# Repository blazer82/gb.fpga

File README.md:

[![verilator-lint-badge]](https://github.com/blazer82/gb.fpga/actions?workflow=verilator-lint)

# FPGAMB0 - FPGA-based Handheld Console

This repository contains the PCB design files as well as the HDL sources for an FPGA-based handheld console that plays games from Gameboy cartridges.

## Demo (GIF)

## Testbenches

Testbench files can be run and analyzed using _iverilog_ and _GTKWave_:

```
iverilog -o main src/hdl/ascii_encoder_tb.v && vvp main -lxt2 && open dump.lx2
```

[verilator-lint-badge]: https://github.com/blazer82/gb.fpga/workflows/verilator-lint/badge.svg

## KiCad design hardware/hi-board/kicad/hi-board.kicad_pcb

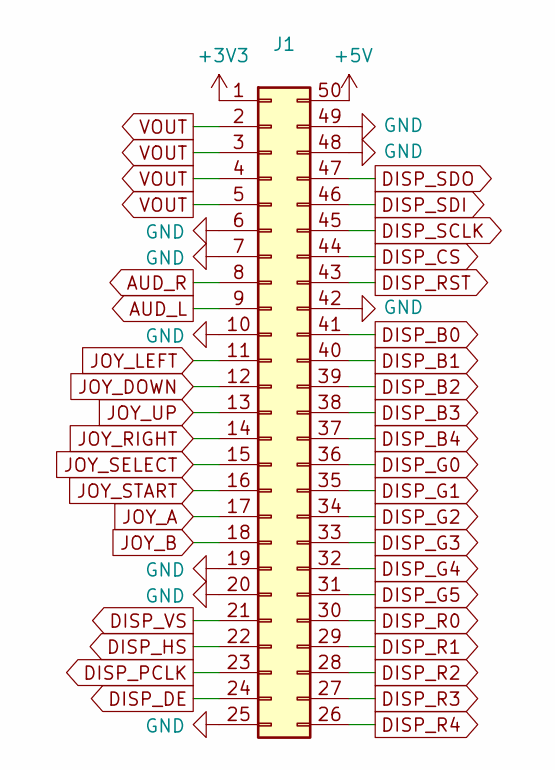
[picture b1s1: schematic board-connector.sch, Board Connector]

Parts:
J1: Conn_02x25_Counter_Clockwise; Hirose_FH12-50S-0.5SH_1x50-1MP_P0.50mm_Horizontal

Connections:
unnamed: J1.2, J1.3, J1.4, J1.5
unnamed: J1.6, J1.7, J1.10, J1.19, J1.20, J1.25, J1.42, J1.48, J1.49

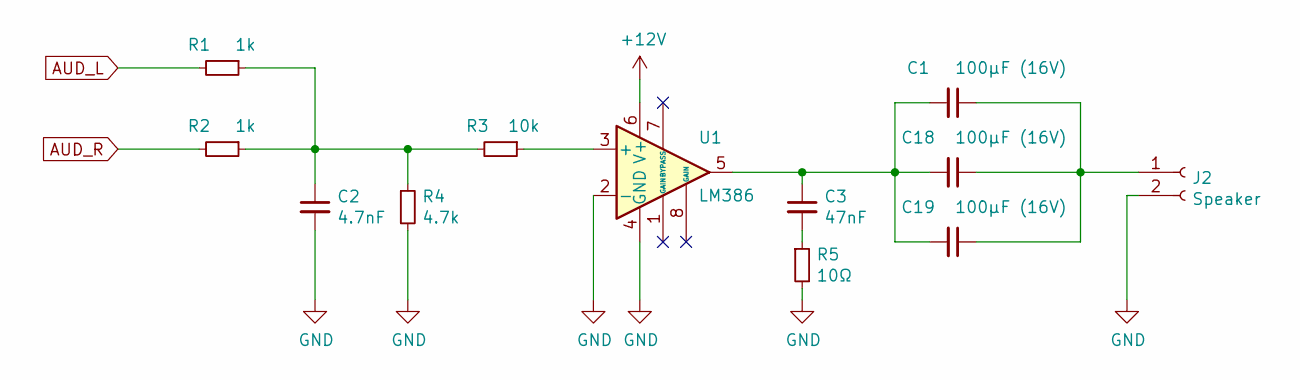
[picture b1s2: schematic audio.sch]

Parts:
C1, C18, C19: 100µF (16V); C_1210_3225Metric
C2: 4.7nF; C_0603_1608Metric
C3: 47nF; C_0603_1608Metric
J2: Speaker; PinHeader_1x02_P2.54mm_Vertical
R1, R2: 1k; R_0603_1608Metric
R3: 10k; R_0603_1608Metric
R4: 4.7k; R_0603_1608Metric
R5: 10Ω; R_0603_1608Metric
U1: LM386; VSSOP-8_3.0x3.0mm_P0.65mm

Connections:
+12V: U1.6 (V+); also elsewhere on the board
AUD_L: R1.2; also elsewhere on the board
AUD_R: R2.2; also elsewhere on the board
GND: C2.2, J2.2, R4.2, R5.2, U1.2 (-), U1.4 (GND); also elsewhere on the board
unnamed: C1.1, C18.1, C19.1, J2.1
unnamed: C1.2, C3.1, C18.2, C19.2, U1.5
unnamed: C2.1, R1.1, R2.1, R3.2, R4.1
unnamed: C3.2, R5.1
unnamed: R3.1, U1.3 (+)

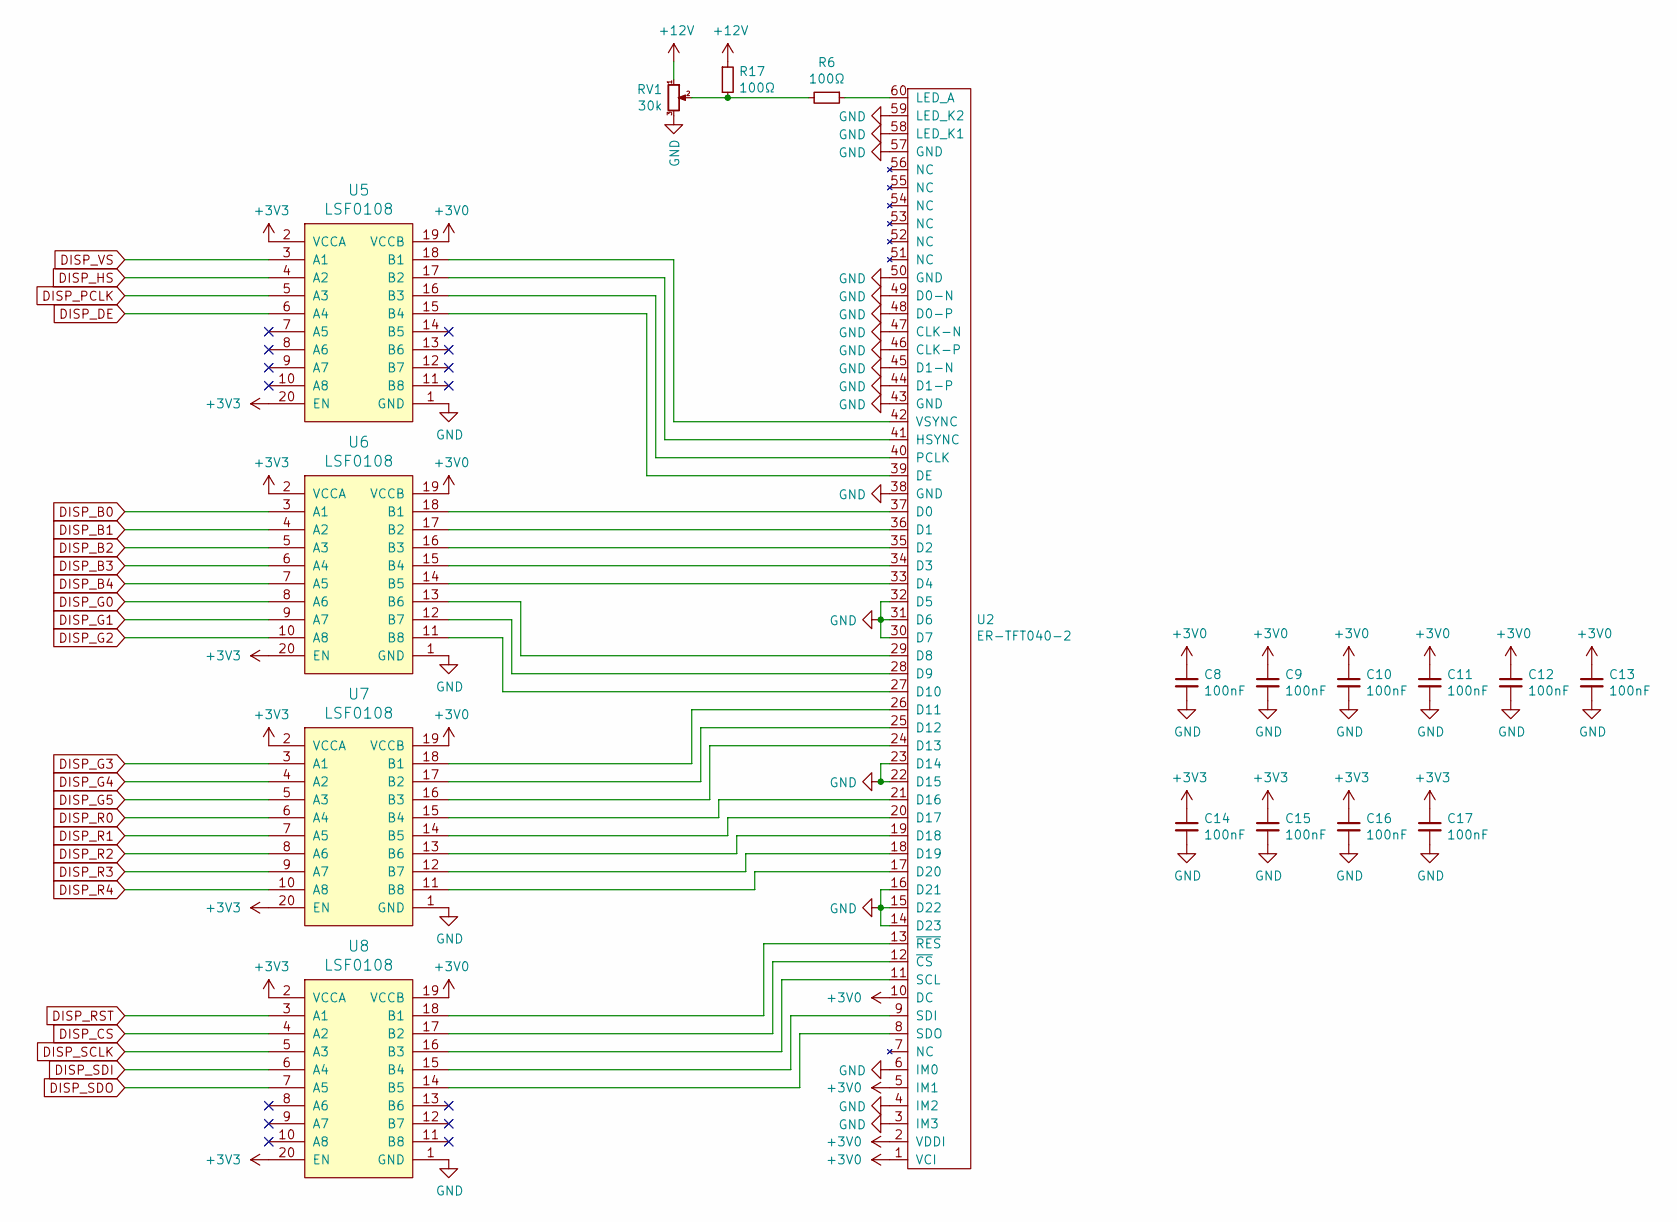
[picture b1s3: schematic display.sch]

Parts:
C8, C9, C10, C11, C12, C13, C14, C15, C16, C17: 100nF; C_0603_1608Metric
R6, R17: 100Ω; R_0603_1608Metric
RV1: 30k; Dual_Pot
U2: ER-TFT040-2; HRS_FH28-60S-0.5SH(05)
U5, U6, U7, U8: LSF0108; TSSOP-20_4.4x6.5mm_P0.65mm

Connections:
+3V0: C8.1, C9.1, C10.1, C11.1, C12.1, C13.1, U2.1 (VCI), U2.2 (VDDI), U2.5 (IM1), U2.10 (DC), U5.19 (VCCB), U6.19 (VCCB), U7.19 (VCCB), U8.19 (VCCB); also elsewhere on the board
+3V3: C14.1, C15.1, C16.1, C17.1, U5.2 (VCCA), U5.20 (EN), U6.2 (VCCA), U6.20 (EN), U7.2 (VCCA), U7.20 (EN), U8.2 (VCCA), U8.20 (EN); also elsewhere on the board
+12V: R17.1, RV1.1; also elsewhere on the board
DISP_B0: U6.3 (A1); also elsewhere on the board
DISP_B1: U6.4 (A2); also elsewhere on the board
DISP_B2: U6.5 (A3); also elsewhere on the board
DISP_B3: U6.6 (A4); also elsewhere on the board
DISP_B4: U6.7 (A5); also elsewhere on the board
DISP_CS: U8.4 (A2); also elsewhere on the board
DISP_DE: U5.6 (A4); also elsewhere on the board
DISP_G0: U6.8 (A6); also elsewhere on the board
DISP_G1: U6.9 (A7); also elsewhere on the board
DISP_G2: U6.10 (A8); also elsewhere on the board
DISP_G3: U7.3 (A1); also elsewhere on the board
DISP_G4: U7.4 (A2); also elsewhere on the board
DISP_G5: U7.5 (A3); also elsewhere on the board
DISP_HS: U5.4 (A2); also elsewhere on the board
DISP_PCLK: U5.5 (A3); also elsewhere on the board
DISP_R0: U7.6 (A4); also elsewhere on the board
DISP_R1: U7.7 (A5); also elsewhere on the board
DISP_R2: U7.8 (A6); also elsewhere on the board
DISP_R3: U7.9 (A7); also elsewhere on the board
DISP_R4: U7.10 (A8); also elsewhere on the board
DISP_RST: U8.3 (A1); also elsewhere on the board
DISP_SCLK: U8.5 (A3); also elsewhere on the board
DISP_SDI: U8.6 (A4); also elsewhere on the board
DISP_SDO: U8.7 (A5); also elsewhere on the board
DISP_VS: U5.3 (A1); also elsewhere on the board
GND: C8.2, C9.2, C10.2, C11.2, C12.2, C13.2, C14.2, C15.2, C16.2, C17.2, RV1.3, U2.3 (IM3), U2.4 (IM2), U2.6 (IM0), U2.14 (D23), U2.15 (D22), U2.16 (D21), U2.22 (D15), U2.23 (D14), U2.30 (D7), U2.31 (D6), U2.32 (D5), U2.38 (GND), U2.43 (GND), U2.44 (D1-P), U2.45 (D1-N), U2.46 (CLK-P), U2.47 (CLK-N), U2.48 (D0-P), U2.49 (D0-N), U2.50 (GND), U2.57 (GND), U2.58 (LED_K1), U2.59 (LED_K2), U5.1 (GND), U6.1 (GND), U7.1 (GND), U8.1 (GND); also elsewhere on the board
unnamed 48: R6.1, U2.60 (LED_A); also elsewhere on the board
unnamed: R6.2, R17.2, RV1.2
unnamed 55: U2.8 (SDO), U8.14 (B5); also elsewhere on the board
unnamed 56: U2.9 (SDI), U8.15 (B4); also elsewhere on the board
unnamed 57: U2.11 (SCL), U8.16 (B3); also elsewhere on the board
unnamed 58: U2.12 (~CS), U8.17 (B2); also elsewhere on the board
unnamed 59: U2.13 (~RES), U8.18 (B1); also elsewhere on the board
unnamed 60: U2.17 (D20), U7.11 (B8); also elsewhere on the board
unnamed 61: U2.18 (D19), U7.12 (B7); also elsewhere on the board
unnamed 62: U2.19 (D18), U7.13 (B6); also elsewhere on the board
unnamed 63: U2.20 (D17), U7.14 (B5); also elsewhere on the board
unnamed 64: U2.21 (D16), U7.15 (B4); also elsewhere on the board
unnamed 65: U2.24 (D13), U7.16 (B3); also elsewhere on the board
unnamed 66: U2.25 (D12), U7.17 (B2); also elsewhere on the board
unnamed 67: U2.26 (D11), U7.18 (B1); also elsewhere on the board
unnamed 68: U2.27 (D10), U6.11 (B8); also elsewhere on the board
unnamed 69: U2.28 (D9), U6.12 (B7); also elsewhere on the board
unnamed 70: U2.29 (D8), U6.13 (B6); also elsewhere on the board
unnamed 71: U2.33 (D4), U6.14 (B5); also elsewhere on the board
unnamed 72: U2.34 (D3), U6.15 (B4); also elsewhere on the board
unnamed 73: U2.35 (D2), U6.16 (B3); also elsewhere on the board
unnamed 74: U2.36 (D1), U6.17 (B2); also elsewhere on the board
unnamed 75: U2.37 (D0), U6.18 (B1); also elsewhere on the board
unnamed 76: U2.39 (DE), U5.15 (B4); also elsewhere on the board
unnamed 77: U2.40 (PCLK), U5.16 (B3); also elsewhere on the board
unnamed 78: U2.41 (HSYNC), U5.17 (B2); also elsewhere on the board
unnamed 79: U2.42 (VSYNC), U5.18 (B1); also elsewhere on the board

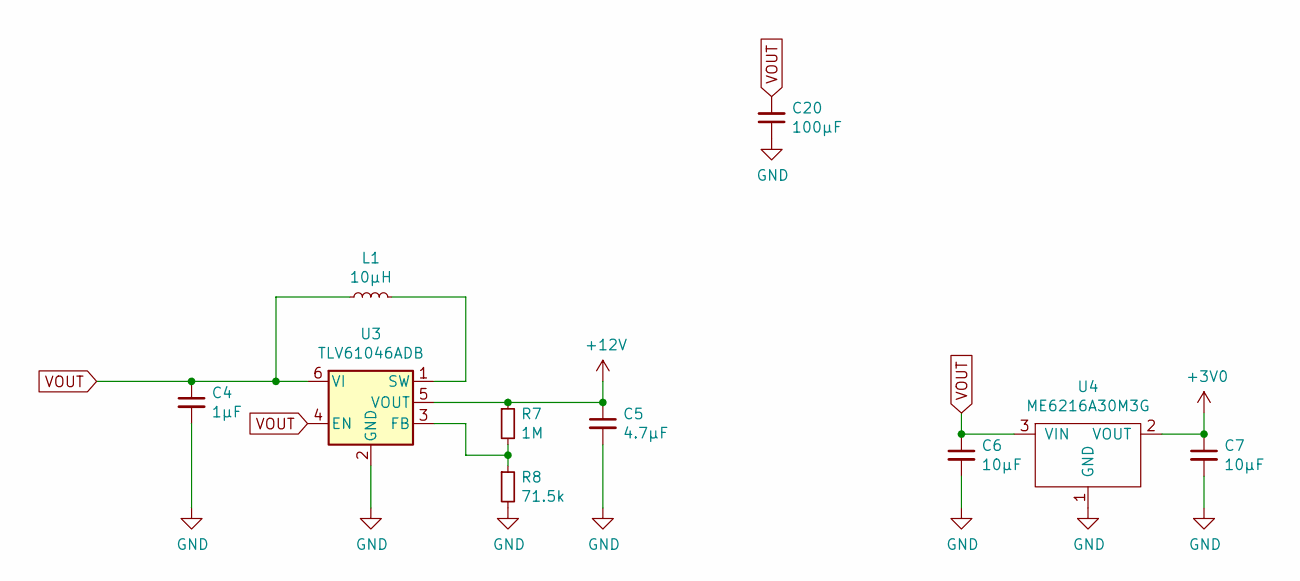
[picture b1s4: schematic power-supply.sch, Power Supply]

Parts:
C4: 1µF; C_0603_1608Metric
C5: 4.7µF; C_0603_1608Metric
C6, C7: 10µF; C_0603_1608Metric
C20: 100µF; C_1210_3225Metric
L1: 10µH; L_0603_1608Metric
R7: 1M; R_0603_1608Metric
R8: 71.5k; R_0603_1608Metric
U3: TLV61046ADB; SOT-23-6
U4: ME6216A30M3G; SOT-23

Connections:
+3V0: C7.1, U4.2 (VOUT); also elsewhere on the board
+12V: C5.1, R7.1, U3.5 (VOUT); also elsewhere on the board
GND: C4.2, C5.2, C6.2, C7.2, C20.1, R8.2, U3.2 (GND), U4.1 (GND); also elsewhere on the board
unnamed: L1.2, U3.1 (SW)
unnamed: R7.2, R8.1, U3.3 (FB)
VOUT: C4.1, C6.1, C20.2, L1.1, U3.4 (EN), U3.6 (VI), U4.3 (VIN); also elsewhere on the board

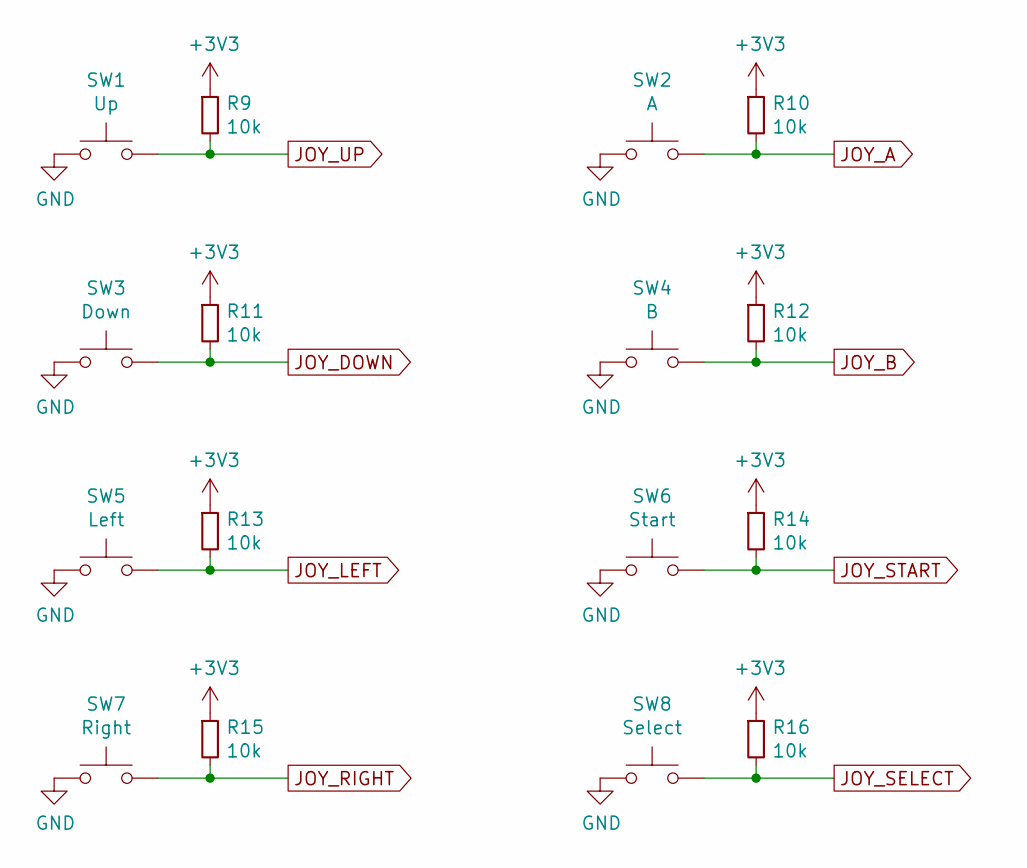
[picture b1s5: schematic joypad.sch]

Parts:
R9, R10, R11, R12, R13, R14, R15, R16: 10k; R_0603_1608Metric
SW1: Up; Rubber_Round
SW2: A; Rubber_Round
SW3: Down; Rubber_Round
SW4: B; Rubber_Round
SW5: Left; Rubber_Round
SW6: Start; Rubber_Square
SW7: Right; Rubber_Round
SW8: Select; Rubber_Square

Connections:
+3V3: R9.1, R10.1, R11.1, R12.1, R13.1, R14.1, R15.1, R16.1; also elsewhere on the board
GND: SW1.1, SW2.1, SW3.1, SW4.1, SW5.1, SW6.1, SW7.1, SW8.1; also elsewhere on the board
JOY_A: R10.2, SW2.2; also elsewhere on the board
JOY_B: R12.2, SW4.2; also elsewhere on the board
JOY_DOWN: R11.2, SW3.2; also elsewhere on the board
JOY_LEFT: R13.2, SW5.2; also elsewhere on the board
JOY_RIGHT: R15.2, SW7.2; also elsewhere on the board
JOY_SELECT: R16.2, SW8.2; also elsewhere on the board
JOY_START: R14.2, SW6.2; also elsewhere on the board
JOY_UP: R9.2, SW1.2; also elsewhere on the board

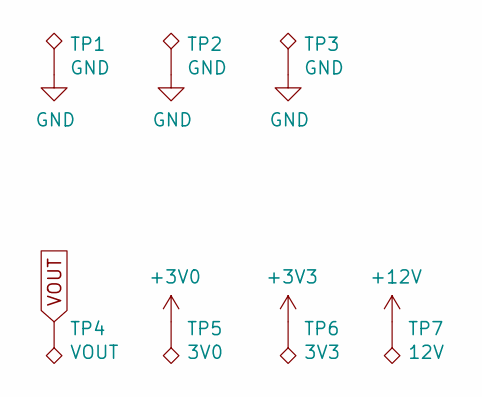
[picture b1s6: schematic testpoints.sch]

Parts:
TP1, TP2, TP3: GND; TestPoint_THTPad_1.5x1.5mm_Drill0.7mm
TP4: VOUT; TestPoint_THTPad_1.0x1.0mm_Drill0.5mm
TP5: 3V0; TestPoint_THTPad_1.0x1.0mm_Drill0.5mm
TP6: 3V3; TestPoint_THTPad_1.0x1.0mm_Drill0.5mm
TP7: 12V; TestPoint_THTPad_1.0x1.0mm_Drill0.5mm

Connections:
+3V0: TP5.1; also elsewhere on the board
+3V3: TP6.1; also elsewhere on the board
+12V: TP7.1; also elsewhere on the board
GND: TP1.1, TP2.1, TP3.1; also elsewhere on the board
VOUT: TP4.1; also elsewhere on the board

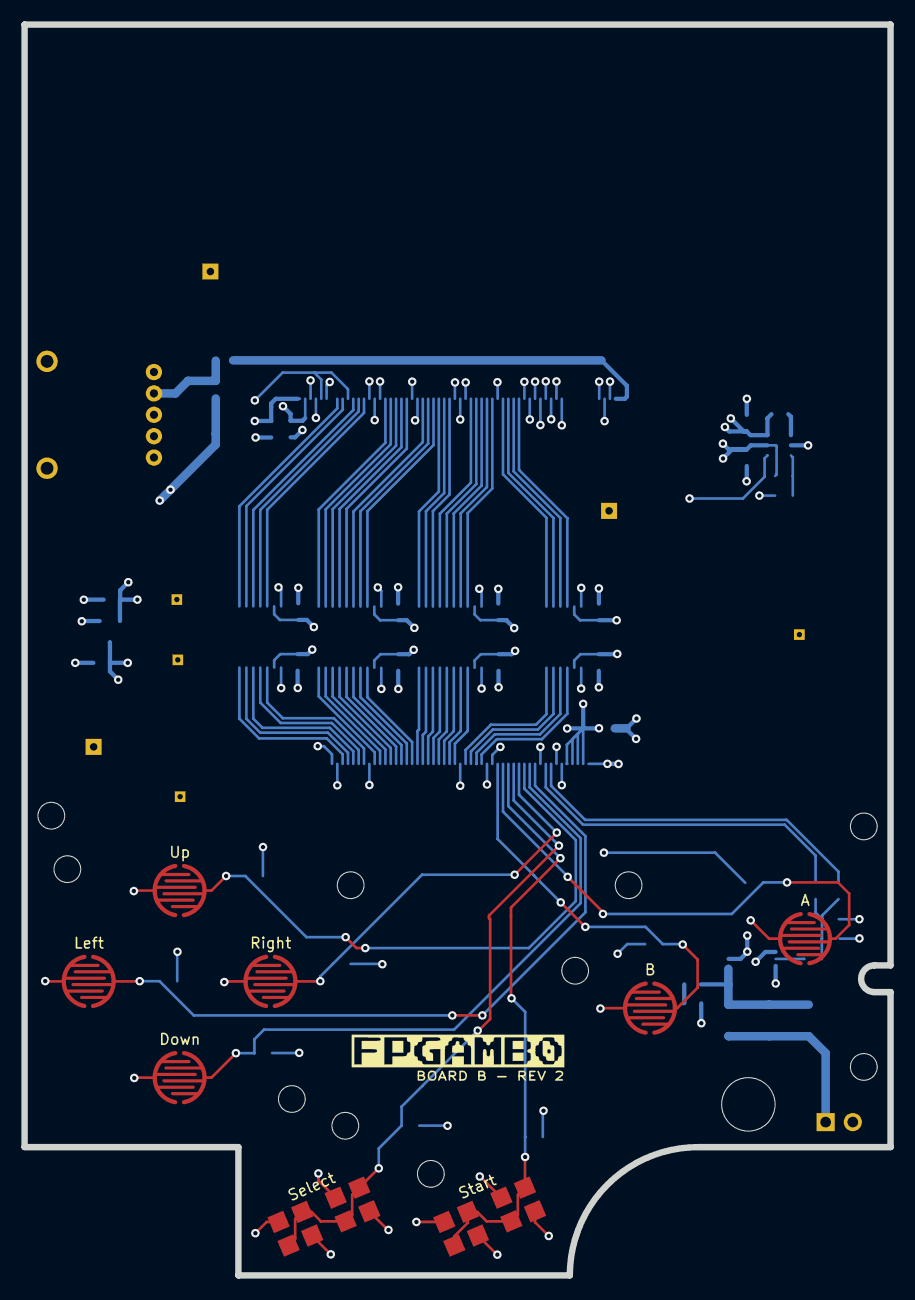
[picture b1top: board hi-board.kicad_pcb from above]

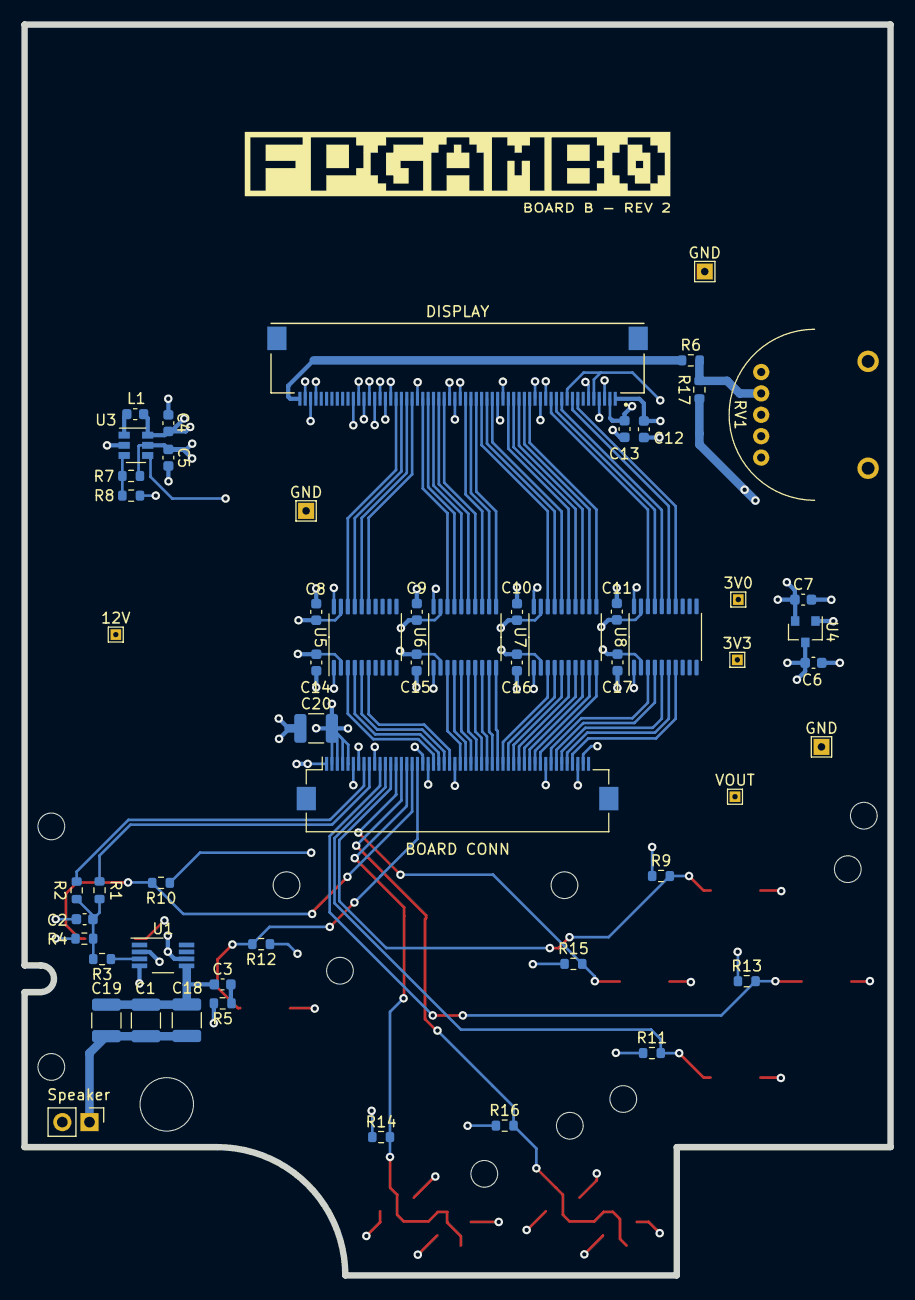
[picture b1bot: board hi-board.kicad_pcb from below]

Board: 4 copper layers, 81.0 x 117.0 mm, 64 parts (56 on the bottom side), 74 nets.

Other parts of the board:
BOARD CONN: Conn_02x25_Counter_Clockwise; Hirose_FH12-50S-0.5SH_1x50-1MP_P0.50mm_Horizontal
DISPLAY: ER-TFT040-2; HRS_FH28-60S-0.5SH(05)

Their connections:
+3V0: DISPLAY.1, DISPLAY.2, DISPLAY.5, DISPLAY.10; also elsewhere on the board
+3V3: BOARD CONN.1; also elsewhere on the board
AUD_L: BOARD CONN.9; also elsewhere on the board
AUD_R: BOARD CONN.8; also elsewhere on the board
DISP_B0: BOARD CONN.26; also elsewhere on the board
DISP_B1: BOARD CONN.27; also elsewhere on the board
DISP_B2: BOARD CONN.28; also elsewhere on the board
DISP_B3: BOARD CONN.29; also elsewhere on the board
DISP_B4: BOARD CONN.30; also elsewhere on the board
DISP_CS: BOARD CONN.44; also elsewhere on the board
DISP_DE: BOARD CONN.24; also elsewhere on the board
DISP_G0: BOARD CONN.31; also elsewhere on the board
DISP_G1: BOARD CONN.32; also elsewhere on the board
DISP_G2: BOARD CONN.33; also elsewhere on the board
DISP_G3: BOARD CONN.34; also elsewhere on the board
DISP_G4: BOARD CONN.35; also elsewhere on the board
DISP_G5: BOARD CONN.36; also elsewhere on the board
DISP_HS: BOARD CONN.22; also elsewhere on the board
DISP_PCLK: BOARD CONN.23; also elsewhere on the board
DISP_R0: BOARD CONN.37; also elsewhere on the board
DISP_R1: BOARD CONN.38; also elsewhere on the board
DISP_R2: BOARD CONN.39; also elsewhere on the board
DISP_R3: BOARD CONN.40; also elsewhere on the board
DISP_R4: BOARD CONN.41; also elsewhere on the board
DISP_RST: BOARD CONN.43; also elsewhere on the board
DISP_SCLK: BOARD CONN.45; also elsewhere on the board
DISP_SDI: BOARD CONN.46; also elsewhere on the board
DISP_SDO: BOARD CONN.47; also elsewhere on the board
DISP_VS: BOARD CONN.21; also elsewhere on the board
GND: BOARD CONN.6, BOARD CONN.7, BOARD CONN.10, BOARD CONN.19, BOARD CONN.20, BOARD CONN.25, BOARD CONN.42, BOARD CONN.48, BOARD CONN.49, DISPLAY.3, DISPLAY.4, DISPLAY.6, DISPLAY.14, DISPLAY.15, DISPLAY.16, DISPLAY.22, DISPLAY.23, DISPLAY.30, DISPLAY.31, DISPLAY.32, DISPLAY.38, DISPLAY.43, DISPLAY.44, DISPLAY.45, DISPLAY.46, DISPLAY.47, DISPLAY.48, DISPLAY.49, DISPLAY.50, DISPLAY.57, DISPLAY.58, DISPLAY.59; also elsewhere on the board
JOY_A: BOARD CONN.17; also elsewhere on the board
JOY_B: BOARD CONN.18; also elsewhere on the board
JOY_DOWN: BOARD CONN.12; also elsewhere on the board
JOY_LEFT: BOARD CONN.11; also elsewhere on the board
JOY_RIGHT: BOARD CONN.14; also elsewhere on the board
JOY_SELECT: BOARD CONN.15; also elsewhere on the board
JOY_START: BOARD CONN.16; also elsewhere on the board
JOY_UP: BOARD CONN.13; also elsewhere on the board
unnamed 48: DISPLAY.60; also elsewhere on the board
unnamed 55: DISPLAY.8; also elsewhere on the board
unnamed 56: DISPLAY.9; also elsewhere on the board
unnamed 57: DISPLAY.11; also elsewhere on the board
unnamed 58: DISPLAY.12; also elsewhere on the board
unnamed 59: DISPLAY.13; also elsewhere on the board
unnamed 60: DISPLAY.17; also elsewhere on the board
unnamed 61: DISPLAY.18; also elsewhere on the board
unnamed 62: DISPLAY.19; also elsewhere on the board
unnamed 63: DISPLAY.20; also elsewhere on the board
unnamed 64: DISPLAY.21; also elsewhere on the board
unnamed 65: DISPLAY.24; also elsewhere on the board
unnamed 66: DISPLAY.25; also elsewhere on the board
unnamed 67: DISPLAY.26; also elsewhere on the board
unnamed 68: DISPLAY.27; also elsewhere on the board
unnamed 69: DISPLAY.28; also elsewhere on the board
unnamed 70: DISPLAY.29; also elsewhere on the board
unnamed 71: DISPLAY.33; also elsewhere on the board
unnamed 72: DISPLAY.34; also elsewhere on the board
unnamed 73: DISPLAY.35; also elsewhere on the board
unnamed 74: DISPLAY.36; also elsewhere on the board
unnamed 75: DISPLAY.37; also elsewhere on the board
unnamed 76: DISPLAY.39; also elsewhere on the board
unnamed 77: DISPLAY.40; also elsewhere on the board
unnamed 78: DISPLAY.41; also elsewhere on the board
unnamed 79: DISPLAY.42; also elsewhere on the board
VOUT: BOARD CONN.2, BOARD CONN.3, BOARD CONN.4, BOARD CONN.5; also elsewhere on the board

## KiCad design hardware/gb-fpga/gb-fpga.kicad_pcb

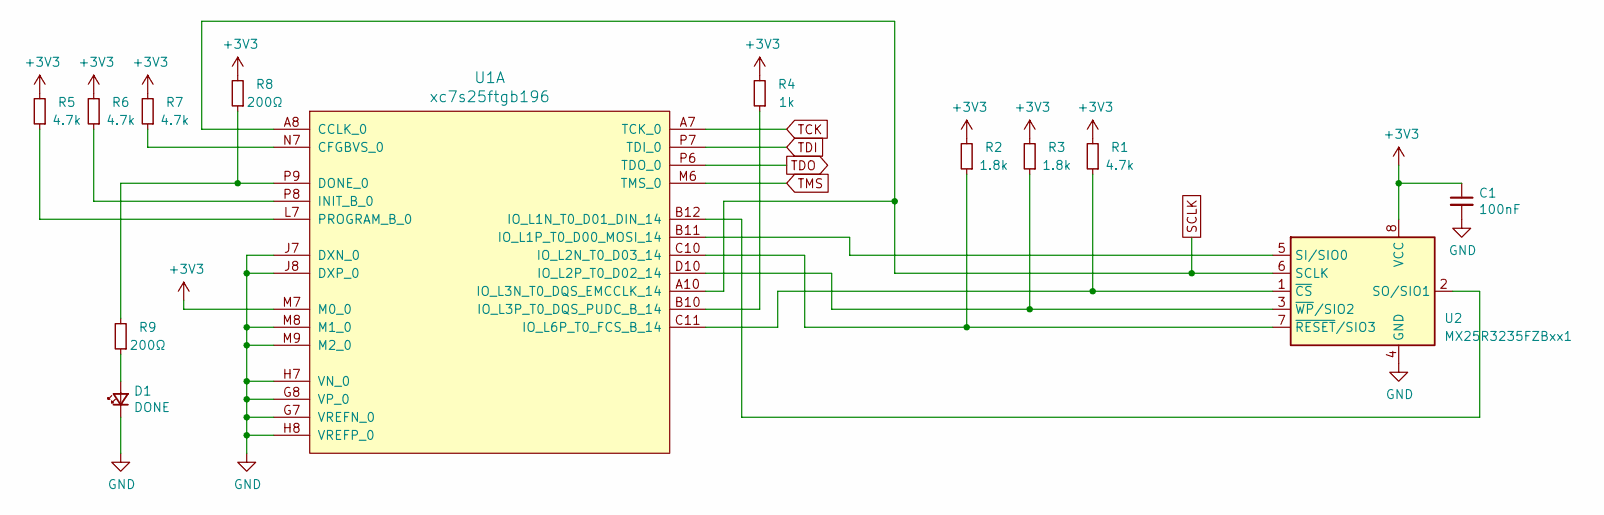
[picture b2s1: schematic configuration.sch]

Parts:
C1: 100nF; C_0402_1005Metric; Manufacturer Part Number CL05B104KO5NNNC
D1: DONE; LED_0402_1005Metric; Manufacturer Part Number NCD0402G1
R1, R5, R6, R7: 4.7k; R_0402_1005Metric; Manufacturer Part Number RC0402JR-074K7L
R2, R3: 1.8k; R_0402_1005Metric; Manufacturer Part Number RC0402JR-071K8L
R4: 1k; R_0402_1005Metric; Manufacturer Part Number RC0402JR-071KL
R8, R9: 200Ω; R_0402_1005Metric; Manufacturer Part Number AC0402JR-07200RL
U1: xc7s25ftgb196; Manufacturer Part Number XC7S25-1FTGB196C
U2: MX25R3235FZBxx1; USON-8_4.0x3.0mm_P0.8mm; Manufacturer Part Number MX25R3235FZBIL0

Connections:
+3V3: C1.1, R1.2, R2.2, R3.2, R4.2, R5.2, R6.2, R7.2, R8.2, U1.M7 (M0_0), U2.8 (VCC); also elsewhere on the board
GND: C1.2, D1.1 (K), U1.G7 (VREFN_0), U1.G8 (VP_0), U1.H7 (VN_0), U1.H8 (VREFP_0), U1.J7 (DXN_0), U1.J8 (DXP_0), U1.M8 (M1_0), U1.M9 (M2_0), U2.4 (GND), U2.9 (GND); also elsewhere on the board
unnamed: D1.2 (A), R9.1
unnamed: R1.1, U1.C11 (IO_L6P_T0_FCS_B_14), U2.1 (~CS)
unnamed: R2.1, U1.C10 (IO_L2N_T0_D03_14), U2.7 (~RESET~/SIO3)
unnamed: R3.1, U1.D10 (IO_L2P_T0_D02_14), U2.3 (~WP~/SIO2)
unnamed: R4.1, U1.B10 (IO_L3P_T0_DQS_PUDC_B_14)
unnamed: R5.1, U1.L7 (PROGRAM_B_0)
unnamed: R6.1, U1.P8 (INIT_B_0)
unnamed: R7.1, U1.N7 (CFGBVS_0)
unnamed: R8.1, R9.2, U1.P9 (DONE_0)
unnamed: U1.B11 (IO_L1P_T0_D00_MOSI_14), U2.5 (SI/SIO0)
unnamed: U1.B12 (IO_L1N_T0_D01_DIN_14), U2.2 (SO/SIO1)
SCLK: U1.A8 (CCLK_0), U1.A10 (IO_L3N_T0_DQS_EMCCLK_14), U2.6 (SCLK); also elsewhere on the board
TCK: U1.A7 (TCK_0); also elsewhere on the board
TDI: U1.P7 (TDI_0); also elsewhere on the board
TDO: U1.P6 (TDO_0); also elsewhere on the board
TMS: U1.M6 (TMS_0); also elsewhere on the board

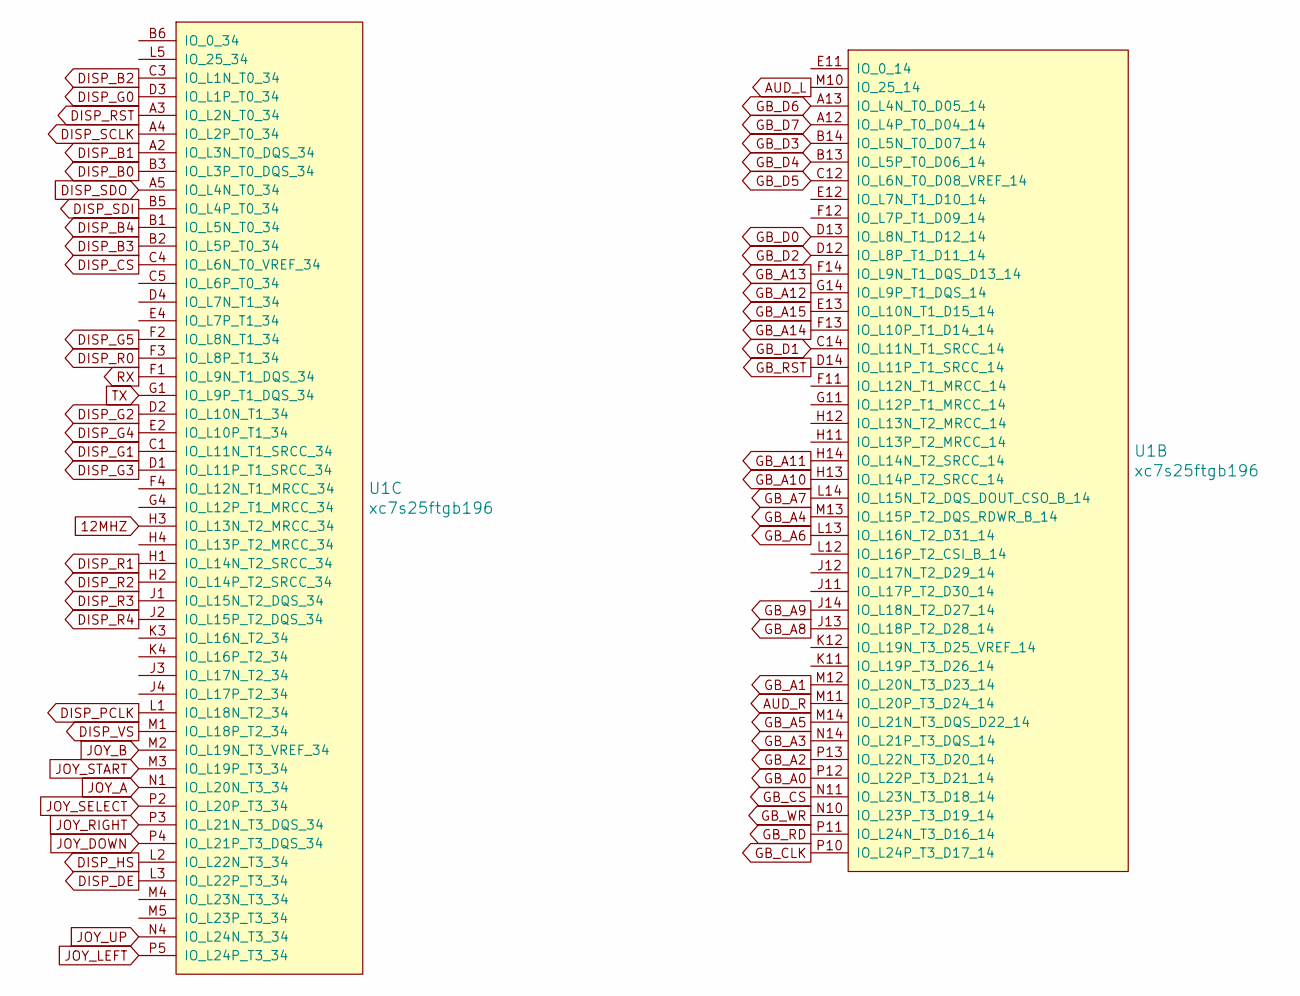
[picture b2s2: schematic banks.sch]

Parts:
U1: xc7s25ftgb196

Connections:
12MHZ: U1.H3 (IO_L13N_T2_MRCC_34); also elsewhere on the board
AUD_L: U1.M10 (IO_25_14); also elsewhere on the board
AUD_R: U1.M11 (IO_L20P_T3_D24_14); also elsewhere on the board
DISP_B0: U1.B3 (IO_L3P_T0_DQS_34); also elsewhere on the board
DISP_B1: U1.A2 (IO_L3N_T0_DQS_34); also elsewhere on the board
DISP_B2: U1.C3 (IO_L1N_T0_34); also elsewhere on the board
DISP_B3: U1.B2 (IO_L5P_T0_34); also elsewhere on the board
DISP_B4: U1.B1 (IO_L5N_T0_34); also elsewhere on the board
DISP_CS: U1.C4 (IO_L6N_T0_VREF_34); also elsewhere on the board
DISP_DE: U1.L3 (IO_L22P_T3_34); also elsewhere on the board
DISP_G0: U1.D3 (IO_L1P_T0_34); also elsewhere on the board
DISP_G1: U1.C1 (IO_L11N_T1_SRCC_34); also elsewhere on the board
DISP_G2: U1.D2 (IO_L10N_T1_34); also elsewhere on the board
DISP_G3: U1.D1 (IO_L11P_T1_SRCC_34); also elsewhere on the board
DISP_G4: U1.E2 (IO_L10P_T1_34); also elsewhere on the board
DISP_G5: U1.F2 (IO_L8N_T1_34); also elsewhere on the board
DISP_HS: U1.L2 (IO_L22N_T3_34); also elsewhere on the board
DISP_PCLK: U1.L1 (IO_L18N_T2_34); also elsewhere on the board
DISP_R0: U1.F3 (IO_L8P_T1_34); also elsewhere on the board
DISP_R1: U1.H1 (IO_L14N_T2_SRCC_34); also elsewhere on the board
DISP_R2: U1.H2 (IO_L14P_T2_SRCC_34); also elsewhere on the board
DISP_R3: U1.J1 (IO_L15N_T2_DQS_34); also elsewhere on the board
DISP_R4: U1.J2 (IO_L15P_T2_DQS_34); also elsewhere on the board
DISP_RST: U1.A3 (IO_L2N_T0_34); also elsewhere on the board
DISP_SCLK: U1.A4 (IO_L2P_T0_34); also elsewhere on the board
DISP_SDI: U1.B5 (IO_L4P_T0_34); also elsewhere on the board
DISP_SDO: U1.A5 (IO_L4N_T0_34); also elsewhere on the board
DISP_VS: U1.M1 (IO_L18P_T2_34); also elsewhere on the board
GB_A0: U1.P12 (IO_L22P_T3_D21_14); also elsewhere on the board
GB_A1: U1.M12 (IO_L20N_T3_D23_14); also elsewhere on the board
GB_A2: U1.P13 (IO_L22N_T3_D20_14); also elsewhere on the board
GB_A3: U1.N14 (IO_L21P_T3_DQS_14); also elsewhere on the board
GB_A4: U1.M13 (IO_L15P_T2_DQS_RDWR_B_14); also elsewhere on the board
GB_A5: U1.M14 (IO_L21N_T3_DQS_D22_14); also elsewhere on the board
GB_A6: U1.L13 (IO_L16N_T2_D31_14); also elsewhere on the board
GB_A7: U1.L14 (IO_L15N_T2_DQS_DOUT_CSO_B_14); also elsewhere on the board
GB_A8: U1.J13 (IO_L18P_T2_D28_14); also elsewhere on the board
GB_A9: U1.J14 (IO_L18N_T2_D27_14); also elsewhere on the board
GB_A10: U1.H13 (IO_L14P_T2_SRCC_14); also elsewhere on the board
GB_A11: U1.H14 (IO_L14N_T2_SRCC_14); also elsewhere on the board
GB_A12: U1.G14 (IO_L9P_T1_DQS_14); also elsewhere on the board
GB_A13: U1.F14 (IO_L9N_T1_DQS_D13_14); also elsewhere on the board
GB_A14: U1.F13 (IO_L10P_T1_D14_14); also elsewhere on the board
GB_A15: U1.E13 (IO_L10N_T1_D15_14); also elsewhere on the board
GB_CLK: U1.P10 (IO_L24P_T3_D17_14); also elsewhere on the board
GB_CS: U1.N11 (IO_L23N_T3_D18_14); also elsewhere on the board
GB_D0: U1.D13 (IO_L8N_T1_D12_14); also elsewhere on the board
GB_D1: U1.C14 (IO_L11N_T1_SRCC_14); also elsewhere on the board
GB_D2: U1.D12 (IO_L8P_T1_D11_14); also elsewhere on the board
GB_D3: U1.B14 (IO_L5N_T0_D07_14); also elsewhere on the board
GB_D4: U1.B13 (IO_L5P_T0_D06_14); also elsewhere on the board
GB_D5: U1.C12 (IO_L6N_T0_D08_VREF_14); also elsewhere on the board
GB_D6: U1.A13 (IO_L4N_T0_D05_14); also elsewhere on the board
GB_D7: U1.A12 (IO_L4P_T0_D04_14); also elsewhere on the board
GB_RD: U1.P11 (IO_L24N_T3_D16_14); also elsewhere on the board
GB_RST: U1.D14 (IO_L11P_T1_SRCC_14); also elsewhere on the board
GB_WR: U1.N10 (IO_L23P_T3_D19_14); also elsewhere on the board
JOY_A: U1.N1 (IO_L20N_T3_34); also elsewhere on the board
JOY_B: U1.M2 (IO_L19N_T3_VREF_34); also elsewhere on the board
JOY_DOWN: U1.P4 (IO_L21P_T3_DQS_34); also elsewhere on the board
JOY_LEFT: U1.P5 (IO_L24P_T3_34); also elsewhere on the board
JOY_RIGHT: U1.P3 (IO_L21N_T3_DQS_34); also elsewhere on the board
JOY_SELECT: U1.P2 (IO_L20P_T3_34); also elsewhere on the board
JOY_START: U1.M3 (IO_L19P_T3_34); also elsewhere on the board
JOY_UP: U1.N4 (IO_L24N_T3_34); also elsewhere on the board
RX: U1.F1 (IO_L9N_T1_DQS_34); also elsewhere on the board
TX: U1.G1 (IO_L9P_T1_DQS_34); also elsewhere on the board

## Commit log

2021-06-20 Initial
2021-06-20 Add project tcl
2021-06-21 Assign footprint and place fpga on board
2021-06-21 Basic boards setup
2021-06-21 Improve audio output by inversing the pwm counter
2021-06-21 Add physical reset button
2021-06-22 Add hierarchical sheets
2021-06-22 Add GND net
2021-06-22 Use USON footprint for flash memory
2021-06-22 Use human readable names on pcb
2021-06-23 Add board outline
2021-06-23 Move board origin to 0 0
2021-06-23 Add second mounting hole
2021-06-23 Add usb parts
2021-06-23 Add additional mounting holes
2021-06-23 Changes to pcb file
2021-06-23 Add and place cartridge footprint and place usb connector
2021-06-24 Add mounting holes to cartridge footprint
2021-06-24 Rename cartridge symbol
2021-06-24 Add connections to flash ic
2021-06-24 Add local fpga symbol
2021-06-24 Connect flash config circuit
2021-06-25 Replace micro usb with usb type c connector
2021-06-25 Update flash footprint
2021-06-25 Add USB connections
2021-06-26 Add oscillator
2021-06-26 Label cartridge connections
2021-06-26 Add LTC3555
2021-06-27 Add step-down conversion
2021-06-27 Add reverse polarity protection to usb
2021-06-27 Update power circuit
2021-06-27 Use power up sequence recommended for Spartan FPGA
2021-06-28 Switch from 0603 to 0402 footprints
2021-06-28 Add chargeing indicator LED
2021-06-28 Add 5V voltage regulator
2021-06-29 Add capacitor networks to fpga power rails
2021-06-30 Hook up cartridge to translation ics
2021-07-01 Fix cartridge pin out and replace voltage translators
2021-07-01 Add power switch
2021-07-01 Add board connector
2021-07-01 Add signals to board connector
2021-07-02 Add audio filter and volume control to schematic
2021-07-02 Add missing power supplies
2021-07-02 Add volume control footprint
2021-07-03 Update board setup
2021-07-03 Fix volume control pinout
2021-07-03 Fix moved edge cut
2021-07-03 Increase edge cut thickness to increase edge clearance
2021-07-03 Layout some smaller groups
2021-07-03 Place more components
2021-07-04 Place power components
2021-07-04 Fan out part of BGA
2021-07-04 Fan out cartridge pins
2021-07-04 Switch to 0201 footprints for fpga power caps
2021-07-04 Place most fpga caps
2021-07-04 Assign cartridge pins to fpga
2021-07-04 Fan out board connector pins
2021-07-04 Assign board connector pins to fpga
2021-07-04 Fan out the remaining pins
2021-07-05 Layout more components
2021-07-05 Route some components
2021-07-05 Route more components
2021-07-05 Route fpga banks
2021-07-05 Add some more power zones
2021-07-05 Add more tracks and regions
2021-07-06 Complete power planes
2021-07-06 Route all power rails
2021-07-06 Route all signals
2021-07-06 Update silkscreen
2021-07-06 Place remaining cap arrays and fix missing connections
2021-07-06 Update silkscreen and plit gerbers
2021-07-06 Add logo and revision
2021-07-07 Lock logo footprints
2021-07-07 Add test points and update gerber for pcb way
2021-07-07 Recreate fabrication files
2021-07-08 Update bom
2021-07-08 Update footprints and BOM
2021-07-08 Add bom and centroid file
2021-07-09 Fix connection on U4
2021-07-09 Remove reduntant centroid file
2021-07-09 Increase min drill size to 0.3mm
2021-07-09 Update BOM with substitute for flash memory
2021-07-10 Slightly adjust display buffer ip
2021-07-24 Reorganize hardware folder
2021-07-24 Init empty kicad project for hi board
2021-08-02 Add custom boot rom
2021-08-02 Add halt on button press
2021-08-21 Add hardware config files
2021-08-26 Update constraints and top hdl to new board specs
2021-08-26 Update bitstream programming config
2021-08-27 Improve openocd config file
2021-08-27 Add flash programming config (not working as of now)
2021-09-04 Update some board specific params and files
2021-09-04 Update HI board files
2021-09-08 Add module to enable quad mode on spi flash
2021-09-12 Add audio schematic
2021-09-15 Add display and power supply to schematics
2021-09-16 Add joypad schematic
2021-09-17 Remove KiCad back files
2021-09-17 Add gitignore
2021-09-17 Add potentiometer to display schematic
2021-09-19 Add joypad footprints
2021-09-19 Add level shifters
2021-09-19 Complete display schematic and change footprints
2021-09-20 HI board setup
2021-09-23 Add HI board outline
2021-10-08 Add mounting holes
2021-10-08 Add joypad footprints to layout
2021-10-09 Flip mounting holes to bottom side
2021-10-09 Place connector components
2021-10-09 Update audio circuit to SMD only
2021-10-09 Place more caps
2021-10-12 Place remaining fix components
2021-10-13 Add GND layer
2021-10-13 Route all but power rails
2021-10-13 Complete routing of HI board
2021-10-13 Add logo and rev
2021-10-13 Add fabrication files
2021-10-14 Add testpoints
2021-10-14 Update PCB outline
2021-10-27 Fix missing connection on hi board
2021-11-03 Update fab files
2021-11-06 Fix SPI pin configuration
2021-11-07 Delay screen init with safe margin for power up
2021-11-09 Enable cartridge interface
2021-11-09 Rotate screen
2021-11-09 Add joypad support
2021-11-12 Fix data bus wiring
2021-11-13 Fix rgb wiring and switch to proper grayscale output
2021-11-13 Remove unused rom block memory
2021-11-13 Better align vsync to reduce tearing
2021-11-14 Add color gradient filter to output
2021-11-16 Add license and update readme
2021-11-26 Add adapted digilent uart demo
2021-11-26 Toggle halt on serial input
2021-11-27 Add debug output module
2021-11-27 Add module to trigger halt
2021-11-27 Add support for buffer transfers over uart
2021-11-28 Dump address and data bus on halt
2021-11-29 Add opcode debug output
2021-11-29 Prepare halt trigger for finer control
2021-12-01 Add step auto trigger debug
2021-12-06 Improve debug output
2021-12-07 Improve debugging
2021-12-08 Add PPU debug output
2021-12-08 Add debug capabilities on serial port (UART) (#5)
2021-12-08 Clean up track and rename rev
2021-12-08 Fix PPU bug where PPU is supposed to enter mode 0 on disable
2021-12-08 Fix issues with wrapping video buffer
2021-12-10 Double frame rate and remove pseudo vsync
2021-12-11 Use tripple video buffer to avoid tearing
2021-12-11 Use tripple video buffer to avoid tearing (#7)
2021-12-18 Cleanup some of the code
2021-12-18 Add verilator github workflow
2021-12-18 Add analyze badge to readme
2021-12-18 Fix most linting issues
2021-12-18 Rename linter workflow
2021-12-18 Fix more lint issues
2021-12-19 Ignore PINMISSING warnings
2021-12-19 Loosen lint rules for mocks
2021-12-19 Add verilator linting (#8)
2021-12-20 Some cleanup and refactoring
2021-12-23 Re-enable latch warning
2021-12-23 Fix video buffer issues
